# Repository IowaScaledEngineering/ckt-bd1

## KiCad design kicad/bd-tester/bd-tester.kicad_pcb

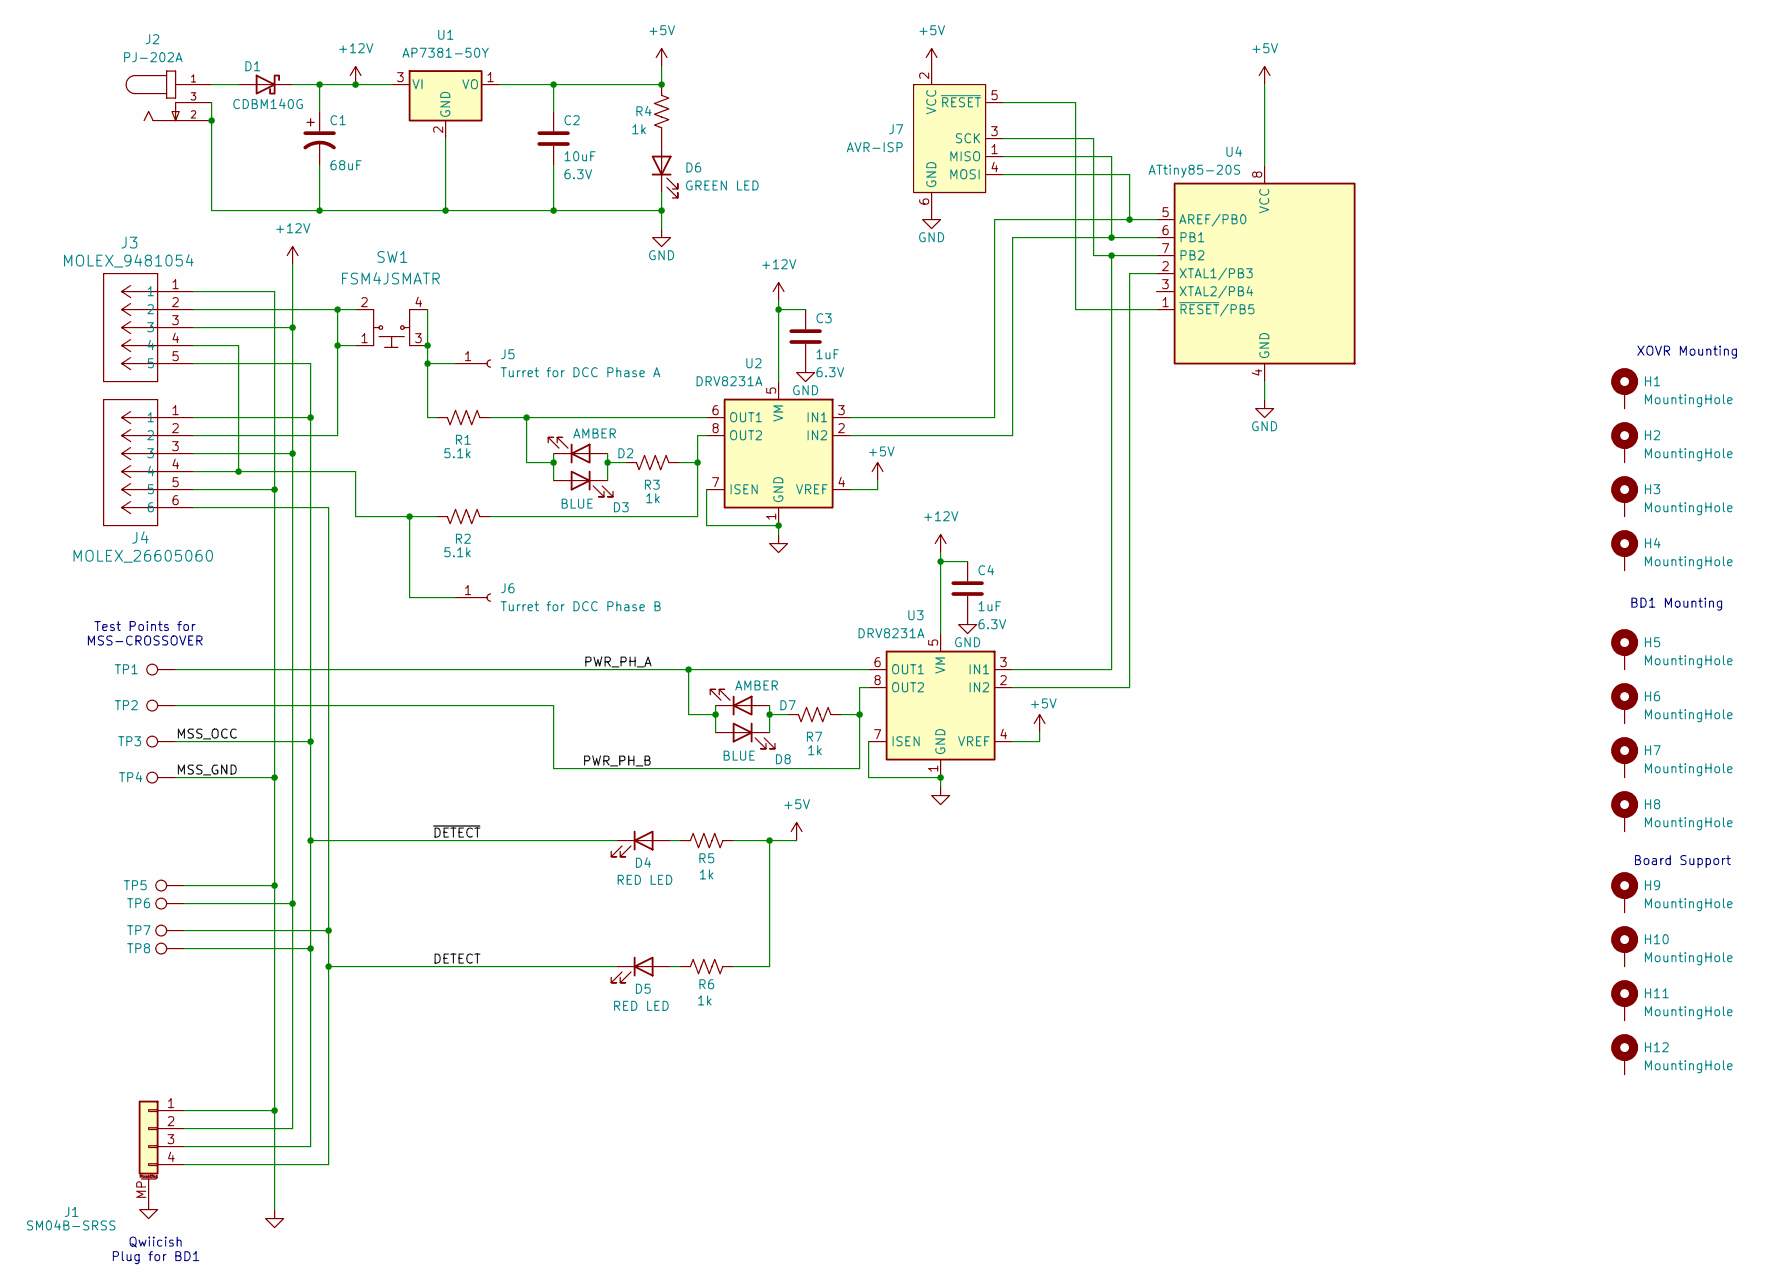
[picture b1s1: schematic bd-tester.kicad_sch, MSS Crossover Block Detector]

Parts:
C1: 68uF; CP_Elec_6.3x5.8
C2: 10uF; C_0805_2012Metric; Voltage 6.3V
C3, C4: 1uF; C_0805_2012Metric; Voltage 6.3V
D1: CDBM140G; SOD-123T
D2, D7: AMBER; LED_0805_2012Metric
D3, D8: BLUE; LED_0805_2012Metric
D4, D5: RED LED; LED_0805_2012Metric
D6: GREEN LED; LED_0805_2012Metric
H1, H2, H3, H4, H5, H6, H7, H8, H9, H10, H11, H12: MountingHole; MountingHole_3.2mm_M3_Pad
J1: SM04B-SRSS; JST_SH_SM04B-SRSS-TB_1x04-1MP_P1.00mm_Horizontal
J2: PJ-202A; CUI_PJ-202A
J3: MOLEX_9481054
J4: MOLEX_26605060
J5: Turret for DCC Phase A; MountingHole_2.7mm_Pad
J6: Turret for DCC Phase B; MountingHole_2.7mm_Pad
J7: AVR-ISP; Tag-Connect_TC2030-IDC-NL_2x03_P1.27mm_Vertical
R1, R2: 5.1k; R_0805_2012Metric
R3, R4, R5, R6, R7: 1k; R_0805_2012Metric
SW1: FSM4JSMATR; TE_FSM4JSMA; MPN FSM4JSMATR; Digi-Key_PN 450-1759-1-ND
TP1, TP5: TestPoint; TestPoint_THTPad_3.0x3.0mm_Drill1.5mm
TP2, TP3, TP4, TP6, TP7, TP8: TestPoint; TestPoint_THTPad_D3.0mm_Drill1.5mm
U1: AP7381-50Y; SOT-89-3
U2, U3: DRV8231A; Texas_HTSOP-8-1EP_3.9x4.9mm_P1.27mm_EP2.95x4.9mm_Mask2.4x3.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
U4: ATtiny85-20S; ATMEL_SO8_DUAL

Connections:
+5V: C2.1, J7.2 (VCC), R4.2, R5.1, R6.1, U1.1 (VO), U2.4 (VREF), U3.4 (VREF), U4.8 (VCC)
+12V: C1.1, C3.1, C4.1, D1.1 (K), J1.2, J3.3, J4.3, TP6.1, U1.3 (VI), U2.5 (VM), U3.5 (VM)
/DETECT: D5.1 (K), J1.4, J4.6, TP7.1
/MSS_OCC: D4.1 (K), J1.3, J3.5, J4.1, TP3.1, TP8.1
/PWR_PH_A: D7.1 (K), D8.2 (A), TP1.1, U3.6 (OUT1)
/PWR_PH_B: R7.2, TP2.1, U3.8 (OUT2)
GND: C1.2, C2.2, C3.2, C4.2, D6.1 (K), J1.1, J1.MP (MountPin), J2.2, J2.3, J3.1, J4.5, J7.6 (GND), TP4.1, TP5.1, U1.2 (GND), U2.1 (GND), U2.7 (ISEN), U2.9 (GND), U3.1 (GND), U3.7 (ISEN), U3.9 (GND), U4.4 (GND)
unnamed: D1.2 (A), J2.1
unnamed: D2.2 (A), D3.1 (K), R3.1
unnamed: D2.1 (K), D3.2 (A), R1.2, U2.6 (OUT1)
unnamed: D4.2 (A), R5.2
unnamed: D5.2 (A), R6.2
unnamed: D6.2 (A), R4.1
unnamed: D7.2 (A), D8.1 (K), R7.1
unnamed: J3.2, J4.2, SW1.1, SW1.2
unnamed: J5.1, R1.1, SW1.3, SW1.4
unnamed: J3.4, J4.4, J6.1, R2.1
unnamed: J7.1 (MISO), U2.2 (IN2), U4.6 (PB1)
unnamed: J7.4 (MOSI), U2.3 (IN1), U4.5 (AREF/PB0)
unnamed: J7.3 (SCK), U3.3 (IN1), U4.7 (PB2)
unnamed: J7.5 (~RESET), U4.1 (~RESET/PB5)
unnamed: R2.2, R3.2, U2.8 (OUT2)
unnamed: U3.2 (IN2), U4.2 (XTAL1/PB3)

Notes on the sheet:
Board Support
Qwiicish Plug for BD1
XOVR Mounting
BD1 Mounting
Test Points for MSS-CROSSOVER

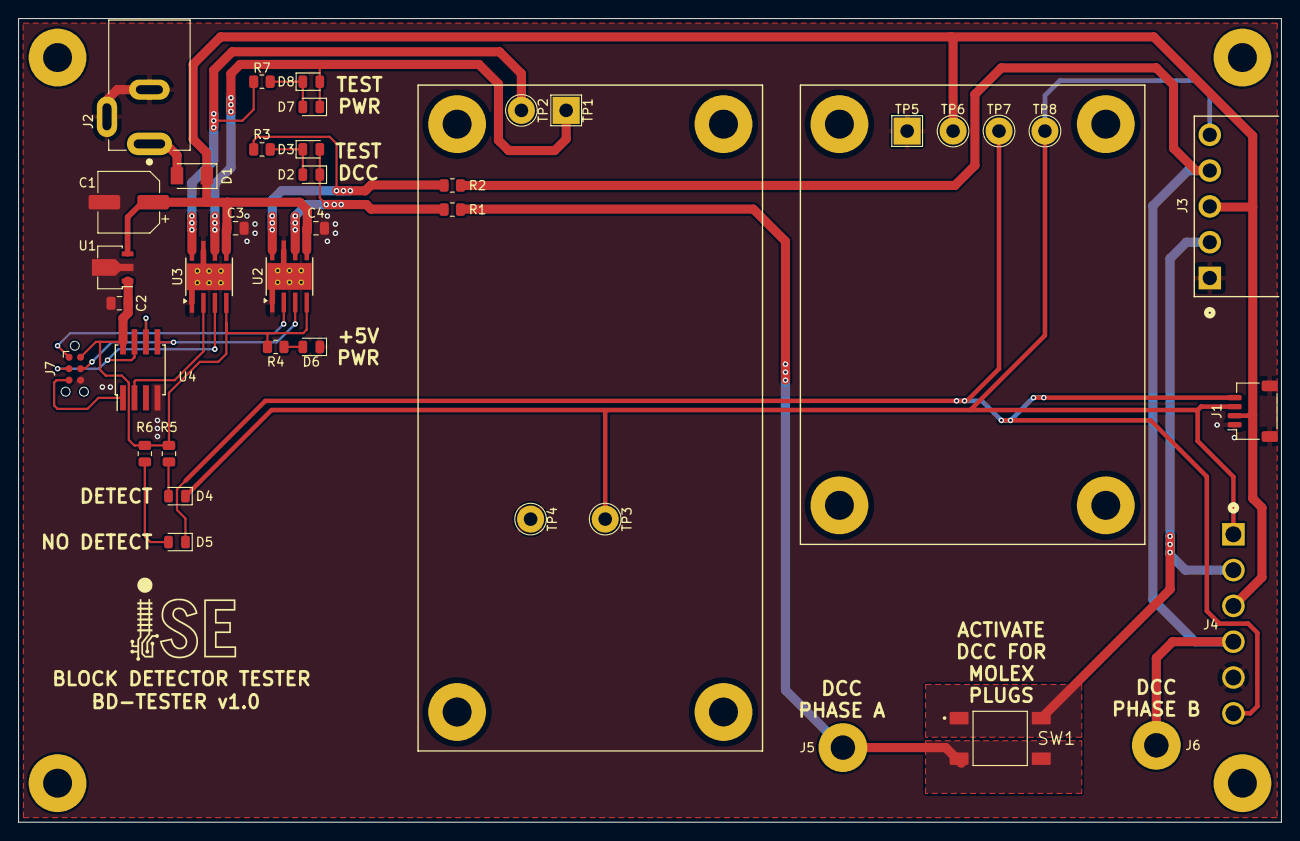
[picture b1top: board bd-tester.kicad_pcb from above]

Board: 2 copper layers, 139.7 x 88.9 mm, 51 parts (0 on the bottom side), 23 nets.

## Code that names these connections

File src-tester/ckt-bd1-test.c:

/*************************************************************************
Title:    CKT-BD1 Test Jig DCC Generator
Authors:  Michael Petersen <railfan@drgw.net>
          Nathan D. Holmes <maverick@drgw.net>
File:     $Id: $
License:  GNU General Public License v3

LICENSE:
    Copyright (C) 2021 Michael Petersen & Nathan Holmes

    This program is free software; you can redistribute it and/or modify
    it under the terms of the GNU General Public License as published by
    the Free Software Foundation; either version 3 of the License, or
    any later version.

    This program is distributed in the hope that it will be useful,
    but WITHOUT ANY WARRANTY; without even the implied warranty of
    MERCHANTABILITY or FITNESS FOR A PARTICULAR PURPOSE.  See the
    GNU General Public License for more details.

*************************************************************************/

#include <stdlib.h>
#include <avr/io.h>
#include <avr/interrupt.h>
#include <avr/wdt.h>
#include <util/delay.h>

#include <avr/io.h>
#include <avr/interrupt.h>
#include <avr/eeprom.h>
#include <util/delay.h>
#include <avr/wdt.h>
#include <util/atomic.h>

static inline void dcc_one()
{
	PORTB ^= _BV(1) | _BV(0);
	_delay_us(58);
	PORTB ^= _BV(1) | _BV(0);
	_delay_us(58);
}

static inline void dcc_zero()
{
	PORTB ^= _BV(1) | _BV(0);
	_delay_us(100);
	PORTB ^= _BV(1) | _BV(0);
	_delay_us(100);
}

void sendPreamble()
{
	for(uint8_t i=0; i<16; i++)
		dcc_one();
}

void sendByte(uint8_t b)
{
	for(uint8_t i=0; i<8; i++)
	{
		if (b & 0x01)
			dcc_one();
		else
			dcc_zero();
		b >>= 1;
	}
}

int main(void)
{
	// Deal with watchdog first thing
	MCUSR = 0;					// Clear reset status

	// Initialization
	wdt_reset();
	wdt_enable(WDTO_250MS);
	wdt_reset();

	// Pin Assignments for PORTB/DDRB
	//  PB0 - Power/Setpoint LED (out)
	//  PB1 - Occupancy LED - Detect (out)
	//  PB2 - /Detect (out)
	//  PB3 - Setpoint button
	//  PB4 - Detector (in, analog, ADC2)
	//  PB5 - Not used
	//  PB6 - Not used
	//  PB7 - Not used
	DDRB  = 0b00111111;
	PORTB = 0b00000001;

	//sei();

	while(1)
	{
		wdt_reset();
		
		// Preamble - 14 ones
		sendPreamble();
		
		dcc_zero(); // Start bit
		
		sendByte(0xFF);

		dcc_zero(); // Start bit
		
		sendByte(0x00);
		
		dcc_zero(); // Start bit
		
		sendByte(0xFF);

		dcc_one(); // End bit
		
		// Send DCC idle packet
	}
}

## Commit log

2016-01-14 Add provision for pull-up resistor
2016-01-14 Oops, forgot to save first
2016-01-14 Update cmri footprint add project file
2016-01-15 BD1 circuit board
2016-01-18 Moved the plus sign for one LED
2016-01-18 Minor review cleanup
2016-01-18 Modifications per design review, part 2 Add R9 for pulling up the other lead
2016-02-05 PG of v1.0
2016-02-14 First cut of working firmware
2016-02-14 Fix ADC2/ADC3 being backwards
2016-02-14 Initial draft of BD1 manual
2016-02-14 Added a few more "features" to the manual
2016-02-21 Diagram for user manual
2018-01-03 New symbol for SOT26 diode
2018-01-03 Modify BD1 to use SOT26 diode
2018-01-05 New v2.0 design based on testing to remove VBIAS
2018-01-05 Minor refdes cleanup
2018-01-06 Updated voltage range. Added new logo. Minor formatting changes.
2018-01-06 Remove 78L33 text from regulator
2018-01-06 Updates per Michael's review
2018-01-29 Sent to fab v2.0
2018-11-18 Force PB0 on. Makes modified v1.0 look like v2.0.
2018-11-18 Bag top
2019-10-21 Modify code for BD1 v2.0 based on attiny13a
2019-10-22 Cleanup around EFUSE and add our programmer defines
2020-01-28 Fixed bug where the ADC was getting retriggered by EVENT_DO_ADC_RUN not getting cleared once the conversion process had started
2020-04-14 BD1 v3 - changed out pot for switch, added set indicator LED, fixed + on other two LEDs
2020-04-14 Fix to move button away from screw hole
2020-04-14 Add missing pushbutton symbol
2020-04-15 Sent to fab 4/15/2020
2020-06-21 Added calibration board
2020-06-22 Added planes to top side and some extra text
2020-07-04 Sent to fab 7/2
2020-07-20 New firmware for pushbutton set bd1 - v3.0
2021-02-11 Add tester PCB and SCH
2021-02-11 A few minor revisions to the tester
2021-02-12 Forgot the outline layer
2021-02-12 Decrease tester hole size on J1/J2 to accomodate pogos
2021-02-19 Fix C1/C1A text
2021-02-22 Add bd1 test jig pg
2021-08-08 Add eval board for v4 front end
2021-08-16 Add ckt-bd1-v4eval
2021-10-18 Initial draft v4 schematic
2021-10-19 v4 sch and pcb
2021-10-27 Add JST connector
2021-10-27 Minor tweak
2021-10-27 Stuff
2021-10-27 Fix note about transformer wiring
2021-10-27 Maybe added calibration? Might work?
2021-10-28 PG 4.0
2021-10-28 Revert "PG 4.0"
    This reverts commit 013a514e4aae1a2b9016e1cb27fa46fe1efc0ed1.
2021-10-28 Fix issue with WDT
2021-10-28 Pull back under 5mm
2021-10-28 Revert "Pull back under 5mm"
    This reverts commit 931aaa442d37beda5219071a60c94a440bb77a99.
2021-11-01 Add pg v4.0
2021-11-20 Working BD1!
2021-11-20 Fix code for going from dma to count
2021-11-22 Add in test harness for ct linearize functionality - temporary
2021-11-22 Fix linearizer code, reformat
2021-11-22 No idea what's changed since last time
2021-11-22 Additional testing for the linearizer code
2021-11-22 Modify v4.0 PCB to have 170mil hole-edge spacing - the two at the bottom were wrong Change tester to remove pointless crystal and match new 4.0A board hole spacing
2021-11-22 Change tester version back to v4.0A and remove bottom silk BD1 outline
2022-05-15 Add v4.0A bd1 and tester
2022-06-05 Add source for test jig
2022-06-09 Update to allow for either INA180 or INA181 to deal with supply chain issues
2022-09-01 Remove R-pack for better mass assembly
2022-09-11 Add solder jumpers and built-in pull up resistors
2022-09-18 Change Molex to 6 pin so as to also bring out the DETECT line - potentially for Circuitron use.
2022-09-19 Center the 6-pin connector, reroute a bunch of stuff
2022-09-19 Change text
2022-10-09 Added panelized array
2022-10-15 Pick and place files
2022-10-16 Added tabs between boards
2022-10-16 Add missing symbols
2022-10-16 Add arrayed BD1s v4.1 now with inter-BD tabs
2022-10-27 Usermanual draft material
2022-10-27 Updated to latest version
2022-10-27 Updated branding
2022-12-03 Add schematic PDF to the v4.1 array
2022-12-06 BD1 manual updates
2022-12-13 Updated manual
2022-12-13 Initial label
2022-12-14 Packaging items
2022-12-15 Add programming script
2023-02-11 Removed pnp files
2023-02-24 6x and 12x brackets
2023-02-24 Updated manual and label files
2023-05-17 Added 12x labels, updated print settings.
2024-04-17 Add tiny25 programming stuff
2025-01-08 Removed labels
2025-05-09 Moved gcode
2026-03-17 Add combined BD tester
2026-03-18 DRC cleanup
2026-06-18 Source for bd1-tester board
2026-06-20 Add bd-tester pg v1.0
